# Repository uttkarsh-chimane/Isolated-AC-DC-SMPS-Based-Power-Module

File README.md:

<h1 align="center">⚡ Isolated AC-DC SMPS-Based Power Supply using HLK-PM01</h1>

<p align="center">
  <a href="#-overview">Overview</a> •
  <a href="#-features">Features</a> •
  <a href="#%EF%B8%8F-hardware-architecture">Hardware Architecture</a> •
  <a href="#-schematic-highlights">Schematic Highlights</a> •
  <a href="#-pcb-design-insights">PCB Insights</a> •
  <a href="#-specifications">Specifications</a>
</p>

<p align="center">
  A compact, isolated AC-to-DC Switch Mode Power Supply (SMPS) built around the HLK-PM01 module. The design incorporates comprehensive mains input protection, EMI suppression, primary-secondary galvanic isolation, and a regulated 5V DC output, making it suitable for embedded systems, IoT devices, and industrial electronics.
</p>

---

## 📖 Overview

This project presents the design of an **isolated 230VAC to 5VDC power supply** using the **HLK-PM01** AC-DC converter module. The objective was to develop a compact, safe, and reliable power supply suitable for powering embedded systems, microcontrollers, and IoT devices.

The design integrates the essential protection and filtering stages required for a mains-powered supply, including:

- **Input overcurrent protection** using a fuse
- **Inrush current limiting** using an NTC thermistor
- **Surge protection** using an MOV
- **EMI suppression** using X2 & Y2 safety capacitors and a bleeder resistor
- **Primary-secondary galvanic isolation**
- **Output filtering and transient protection** using electrolytic & ceramic capacitors and a TVS diode

---

## 📷 Project Gallery

🧩 **3D PCB Render**

🔌 **PCB Layout**

⚙️ **Schematic**

---

## ✨ Features

- 230VAC input, regulated 5V DC output (see [Specifications](#-specifications) for current rating)
- Isolated design (HLK-PM01 module)
- Fuse protection
- MOV surge protection
- NTC inrush current limiter
- X2 EMI suppression capacitor
- Y2 safety capacitor
- Bleeder resistor
- Output filtering capacitors (electrolytic + ceramic)
- TVS diode protection on the output rail
- LED power indicator
- Compact single-layer PCB
- 7.5 mm creepage/clearance barrier (basic isolation — see note below)
- ERC passed, DRC passed

---

## ⚒️ Hardware Architecture

```
230VAC Input
      │
      ▼
 Fuse Protection
      │
      ▼
NTC Thermistor
      │
      ▼
 MOV + X2 Capacitor
      │
      ▼
 HLK-PM01
(Isolated AC-DC Module)
      │
      ▼
Output Filter
(470µF + 100nF)
      │
      ▼
 TVS Protection
      │
      ▼
LED Indicator
      │
      ▼
5V DC Output
```

---

## 📐 Schematic Highlights

**Input protection**
- 0.5A fuse
- 5D-9 NTC thermistor
- MOV (10D471K)

**EMI suppression**
- X2 safety capacitor
- Y2 safety capacitor
- 1MΩ bleeder resistor

**Power conversion**
- HLK-PM01 isolated AC-DC module (230VAC in, 5V DC out)

**Output stage**
- 470µF electrolytic capacitor
- 100nF ceramic capacitor
- SMBJ5.0A TVS diode (clamps ~9.2V — chosen for fast transient suppression while keeping standoff comfortably above the 5V rail)
- LED status indicator

---

## 🧩 PCB Design Insights

- Designed in **KiCad 10**
- Single-layer PCB
- Primary-secondary isolation maintained throughout layout
- 7.5 mm creepage/clearance barrier — sized for **basic insulation** at this voltage/pollution degree; reinforced insulation per IEC 62368-1 typically calls for wider spacing, so treat this as basic-isolation-only unless re-verified against the applicable standard
- Thick power traces for mains current
- Compact component placement
- ERC: 0 errors
- DRC: 0 errors
- Custom silkscreen labels
- Mounting holes included

---

## 🧪 Applications

- ESP32 / Arduino projects
- IoT devices
- Embedded systems
- Home automation
- Sensor nodes
- Industrial monitoring
- Educational / prototype development

---

## ⚠️ Limitations

- Fixed 5V output
- Output power limited by the HLK-PM01 module's rating
- No short-circuit indicator
- No reverse polarity protection on the output
- No output fuse — input fuse protects against mains-side faults only, not secondary-side shorts
- Indoor use only
- Requires a proper enclosure for mains safety

---

## 🚀 Future Improvements

- Add output fuse
- Add reverse polarity protection
- Add power ON switch
- Add AC power LED
- Improve thermal management
- Add test points
- Add mounting labels
- Design a double-layer version
- Add IEC input connector
- Improve EMI filtering

---

## 📚 Learning Outcomes

- PCB design using KiCad
- AC-DC power supply design
- Electrical isolation concepts (creepage & clearance)
- Component footprint selection
- PCB routing techniques
- EMI suppression methods
- Mains safety practices
- Design Rule Check (DRC) and Electrical Rule Check (ERC)
- PCB 3D visualization

---

## 📊 Specifications

| **Parameter** | **Value** |
|:--------------|:----------|
| **Project** | Isolated 230VAC to 5VDC Power Supply using HLK-PM01 |
| **Input Voltage** | 230 VAC, 50 Hz |
| **Output Voltage** | 5 V DC |
| **Output Power** | 3 W |
| **Output Current** | Up to 600 mA |
| **AC-DC Module** | Hi-Link HLK-PM01 |
| **Input Protection** | 0.5 A Fuse, MOV (10D471K), 5D-9 NTC |
| **EMI Filter** | X2 Capacitor, Y2 Capacitor, 1 MΩ Bleeder |
| **Output Protection** | SMBJ5.0A TVS Diode |
| **Output Filter** | 470 µF + 100 nF Capacitors |
| **Isolation** | Galvanically Isolated (basic, 7.5 mm barrier) |
| **PCB** | Single-Layer FR-4 |
| **Design Software** | KiCad 10 |
| **ERC Status** | ✅ Passed (0 Errors) |
| **DRC Status** | ✅ Passed (0 Errors) |
| **Applications** | ESP32, Arduino, IoT, Embedded Systems |

---

## 👨‍💻 Author

**Uttkarsh Chimane**
---

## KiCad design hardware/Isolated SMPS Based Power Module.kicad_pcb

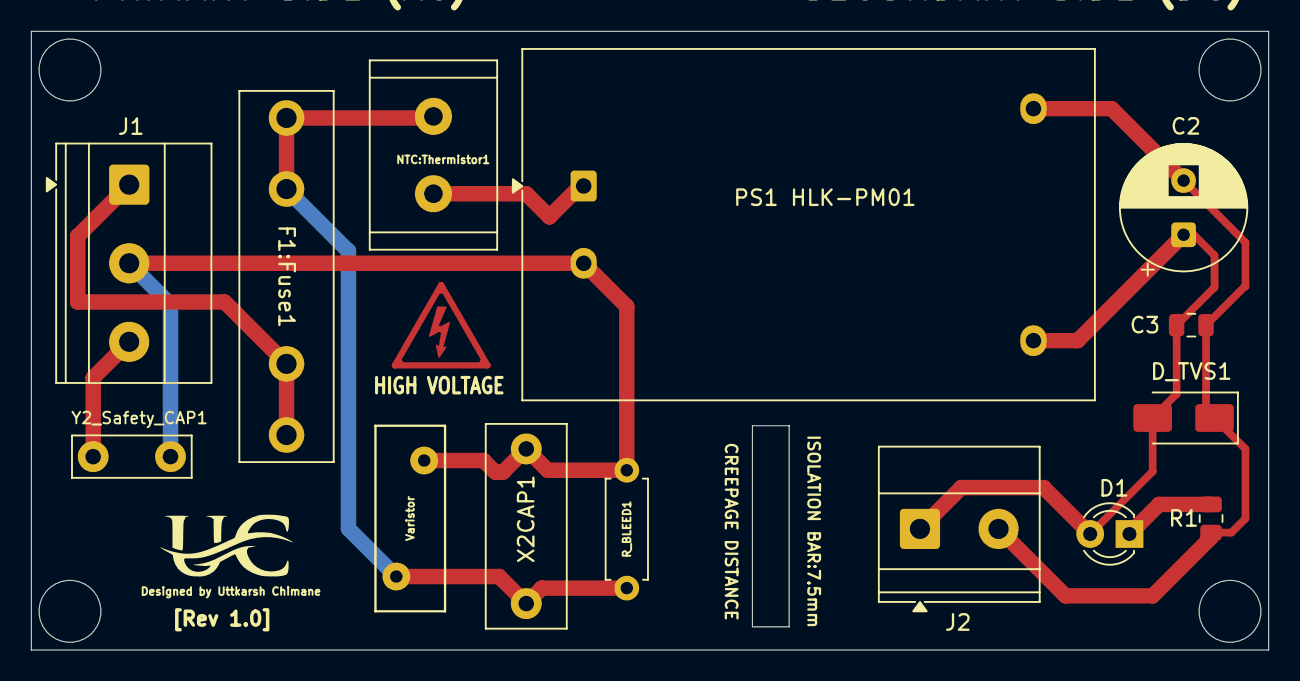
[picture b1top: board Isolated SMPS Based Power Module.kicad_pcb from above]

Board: 2 copper layers, 80.0 x 40.0 mm, 14 parts (0 on the bottom side), 8 nets.

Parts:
C2: 470uF/10V; CP_Radial_D8.0mm_P3.50mm
C3: 100nF; C_0805_2012Metric
D1: LED; LED_D3.0mm
D_TVS1: SMBJ5.0A; D_SMA
F1:Fuse1: 0.5A/250V; Fuseholder_Littelfuse_100_series_5x20mm
J1: AC INPUT; TerminalBlock_Phoenix_MKDS-1,5-3-5.08_1x03_P5.08mm_Horizont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
J2: Screw_Terminal_01x02; TerminalBlock_Phoenix_MKDS-1,5-2-5.08_1x02_P5.08mm_Horizont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
NTC:Thermistor1: 5D-9,Inrush Limiter; R_Radial_Power_L12.0mm_W8.0mm_P5.00mm
PS1 HLK-PM01: HLK-PM01; Converter_ACDC_Hi-Link_HLK-PMxx
R1: 470Ω; R_0805_2012Metric
R_BLEED1: 1MΩ; R_Axial_DIN0207_L6.3mm_D2.5mm_P7.62mm_Horizontal
Varistor: 10D471K; RV_Disc_D12mm_W4.5mm_P7.5mm
X2CAP1: 0.1uF/275VAC; C_Rect_L13.0mm_W5.0mm_P10.00mm_FKS3_FKP3_MKS4
Y2_Safety_CAP1: 2.2nF Y2 250VAC; C_Disc_D7.5mm_W2.5mm_P5.00mm

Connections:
Earth: J1.3, Y2_Safety_CAP1.2
unnamed: F1:Fuse1.2, NTC:Thermistor1.1, R_BLEED1.1, Varistor.1, X2CAP1.1
unnamed: C2.1, C3.1, D1.2 (A), D_TVS1.2 (A2), J2.1, PS1 HLK-PM01.4 (+5V)
unnamed: D1.1 (K), R1.1
unnamed: C2.2, C3.2, D_TVS1.1 (A1), J2.2, PS1 HLK-PM01.3 (GND), R1.2
unnamed: F1:Fuse1.1, J1.1
unnamed: J1.2, PS1 HLK-PM01.2 (AC_N), R_BLEED1.2, Varistor.2, X2CAP1.2, Y2_Safety_CAP1.1
unnamed: NTC:Thermistor1.2, PS1 HLK-PM01.1 (AC_L)
